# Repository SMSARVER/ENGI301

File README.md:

<h1>ENGI301</h1>
<p>Repository for ENGI301 course work</p>

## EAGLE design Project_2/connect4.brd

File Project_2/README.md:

Please read me or else:

This directory contains the files (library, board, schematic, manufacturing) for a custom PCB for my Robot V.S. Human Connect 4 Robot. Please learn more about my project here: https://www.hackster.io/samuelmsarver/robot-v-s-human-connect-4-eca0b5

This PCB was made using EAGLE and contains all components for the robot except for the stepper motor and servo motor (which are attatched externally).

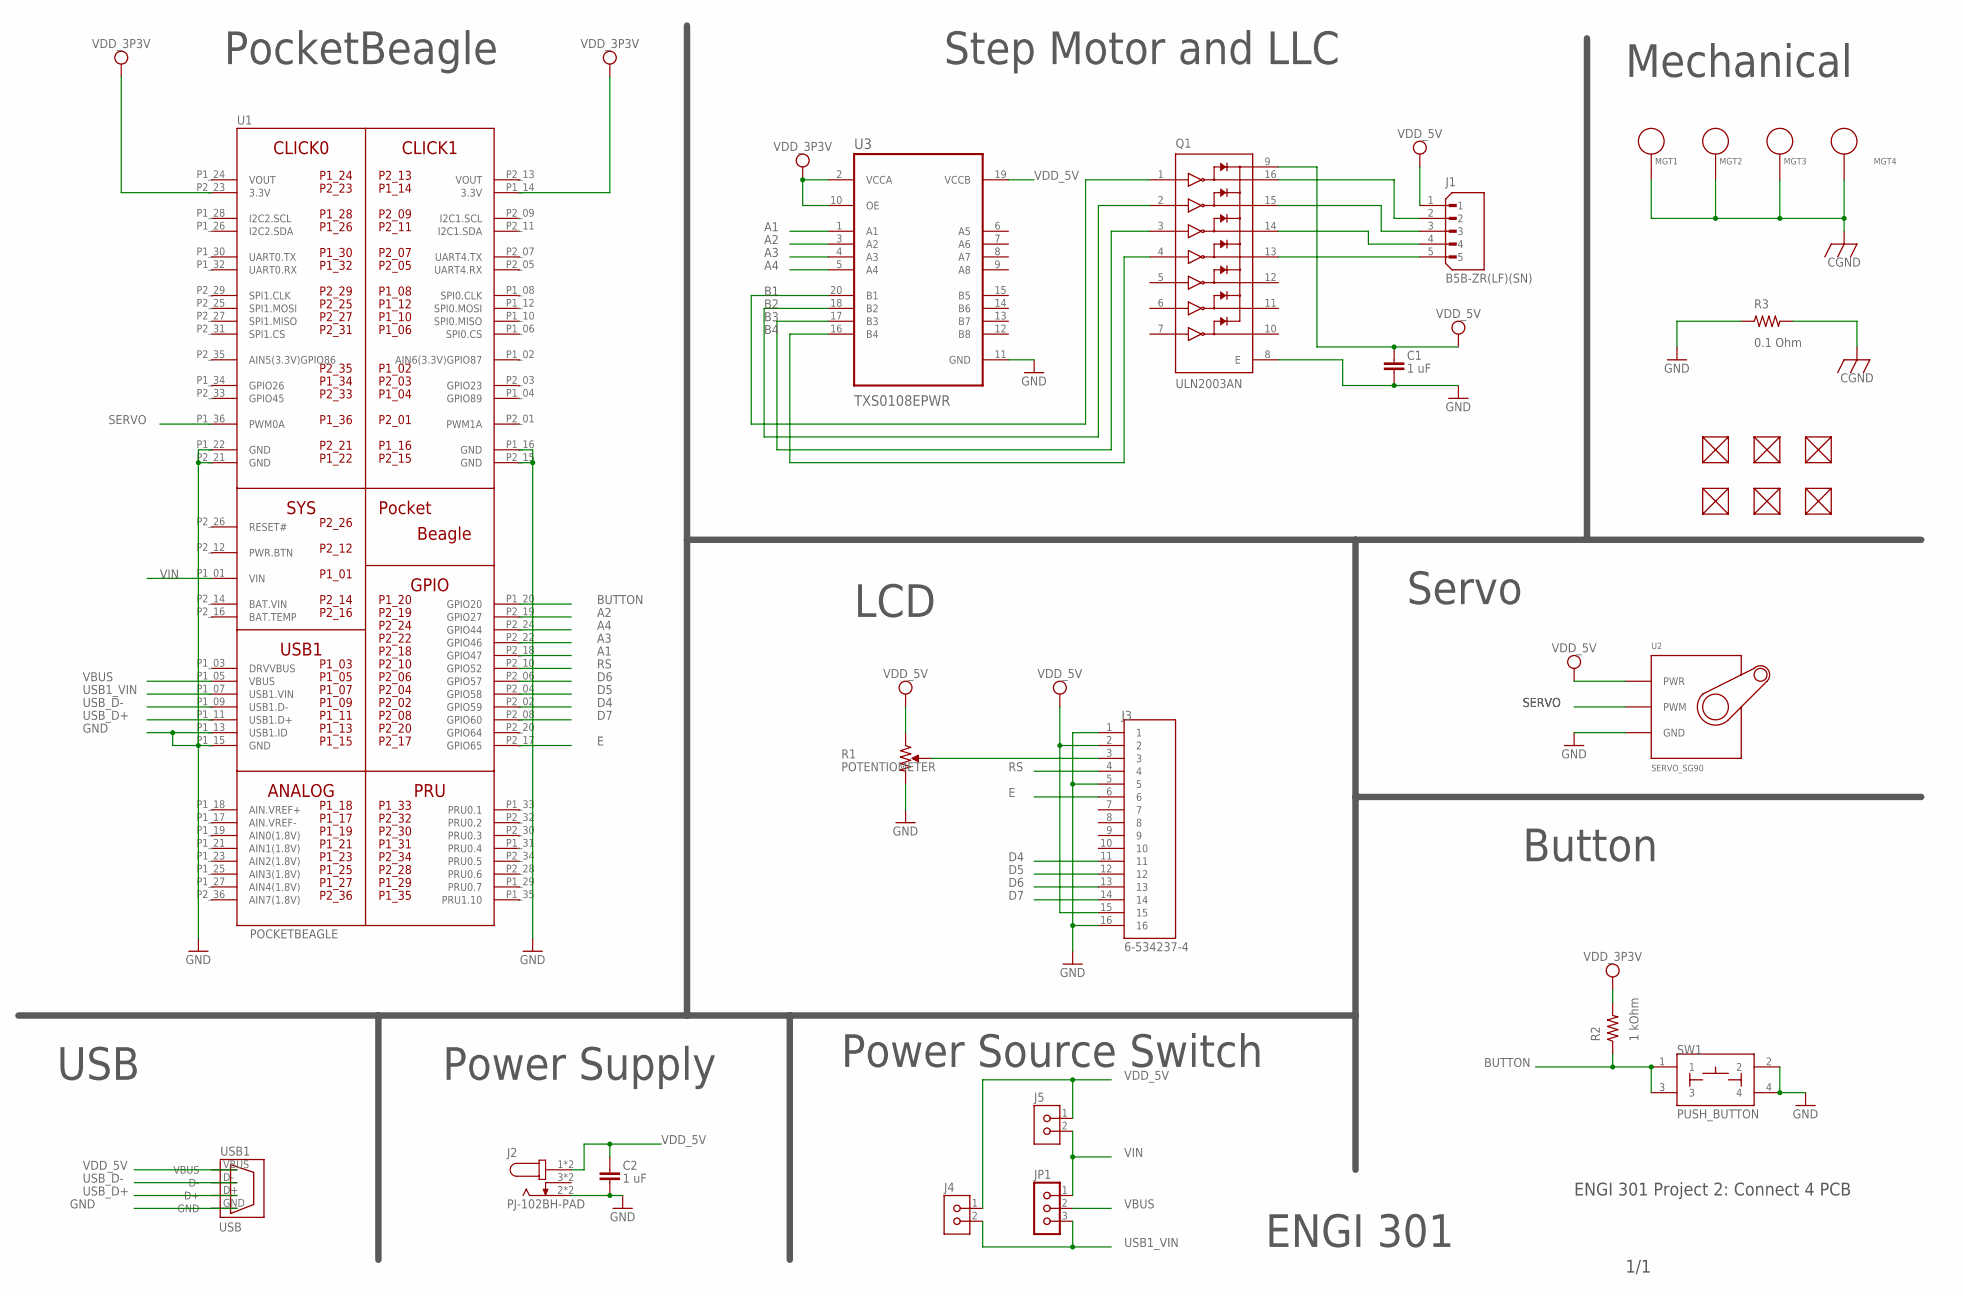
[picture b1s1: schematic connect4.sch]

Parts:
C1, C2: 1 uF; C0402
FUD1, FUD2, FUD3, FUD4, FUD5, FUD6: FIDUCIAL; FIDUCIAL_40MIL
J1: B5B-ZR(LF)(SN); JST_B5B-ZR(LF)(SN)
J2: PJ-102BH-PAD; CUI_PJ-102BH-DIM-SMT-PAD
J3: 6-534237-4; TE_6-534237-4
J4, J5: PINHD-1X2; H1X2-2.54
JP1: PINHD-1X3; H1X3-2.54
MGT1, MGT2, MGT3, MGT4: MOUNTING_HOLE
Q1: ULN2003AN; DIP794W45P254L1969H508Q16
R1: POTENTIOMETER; POT-PO90S
R2: 1 kOhm; R0603
R3: 0.1 Ohm; R0805
SW1: PUSH_BUTTON; BUTTON_12.5MM
U1: POCKETBEAGLE
U2: SERVO_SG90; SERVO-X1
U3: TXS0108EPWR; SOP65P640X120-20N
USB1: USB

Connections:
A1: U1.P2_18 (GPIO47), U3.1 (A1)
A2: U1.P2_19 (GPIO27), U3.3 (A2)
A3: U1.P2_22 (GPIO46), U3.4 (A3)
A4: U1.P2_24 (GPIO44), U3.5 (A4)
B1: Q1.1 (1B), U3.20 (B1)
B2: Q1.2 (2B), U3.18 (B2)
B3: Q1.3 (3B), U3.17 (B3)
B4: Q1.4 (4B), U3.16 (B4)
BAT.VIN: U1.P2_14 (BAT.VIN)
BUTTON: R2.1, SW1.1, SW1.3, U1.P1_20 (GPIO20)
CGND: MGT1.P$1, MGT2.P$1, MGT3.P$1, MGT4.P$1, R3.2
D4: J3.11, U1.P2_02 (GPIO59)
D5: J3.12, U1.P2_04 (GPIO58)
D6: J3.13, U1.P2_06 (GPIO57)
D7: J3.14, U1.P2_08 (GPIO60)
E: J3.6, U1.P2_17 (GPIO65)
GND: C1.2, C2.2, J2.2, J2.2_B (2), J3.1, J3.5, J3.16, Q1.8 (E), R1.CW, R3.1, SW1.2, SW1.4, U1.P1_13 (USB1.ID), U1.P1_15 (GND), U1.P1_16 (GND), U1.P1_22 (GND), U1.P2_15 (GND), U1.P2_21 (GND), U2.GND, U3.11 (GND), USB1.GND
unnamed: J1.2, Q1.16 (1C)
unnamed: J1.3, Q1.15 (2C)
unnamed: J3.3, R1.S
unnamed: J1.4, Q1.14 (3C)
unnamed: J1.5, Q1.13 (4C)
RS: J3.4, U1.P2_10 (GPIO52)
SERVO: U1.P1_36 (PWM0A), U2.SIG (PWM)
USB1_VIN: J4.2, JP1.3, U1.P1_07 (USB1.VIN)
USB_D+: U1.P1_11 (USB1.D+), USB1.D+
USB_D-: U1.P1_09 (USB1.D-), USB1.D-
VBUS: JP1.2, U1.P1_05 (VBUS)
VDD_3P3V: R2.2, U1.P1_14 (3.3V), U1.P2_23 (3.3V), U3.2 (VCCA), U3.10 (OE)
VDD_5V: C1.1, C2.1, J1.1, J2.1, J2.1_B (1), J3.2, J3.15, J4.1, J5.1, Q1.9 (COM), R1.CCW, U2.PWR, U3.19 (VCCB), USB1.VBUS
VIN: J5.2, JP1.1, U1.P1_01 (VIN)
VOUT: U1.P1_24 (VOUT), U1.P2_13 (VOUT)

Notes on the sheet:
PocketBeagle
Step Motor and LLC
LCD
USB
Power Supply
Power Source Switch
Button
Servo
Mechanical
ENGI 301
ENGI 301 Project 2: Connect 4 PCB
1/1

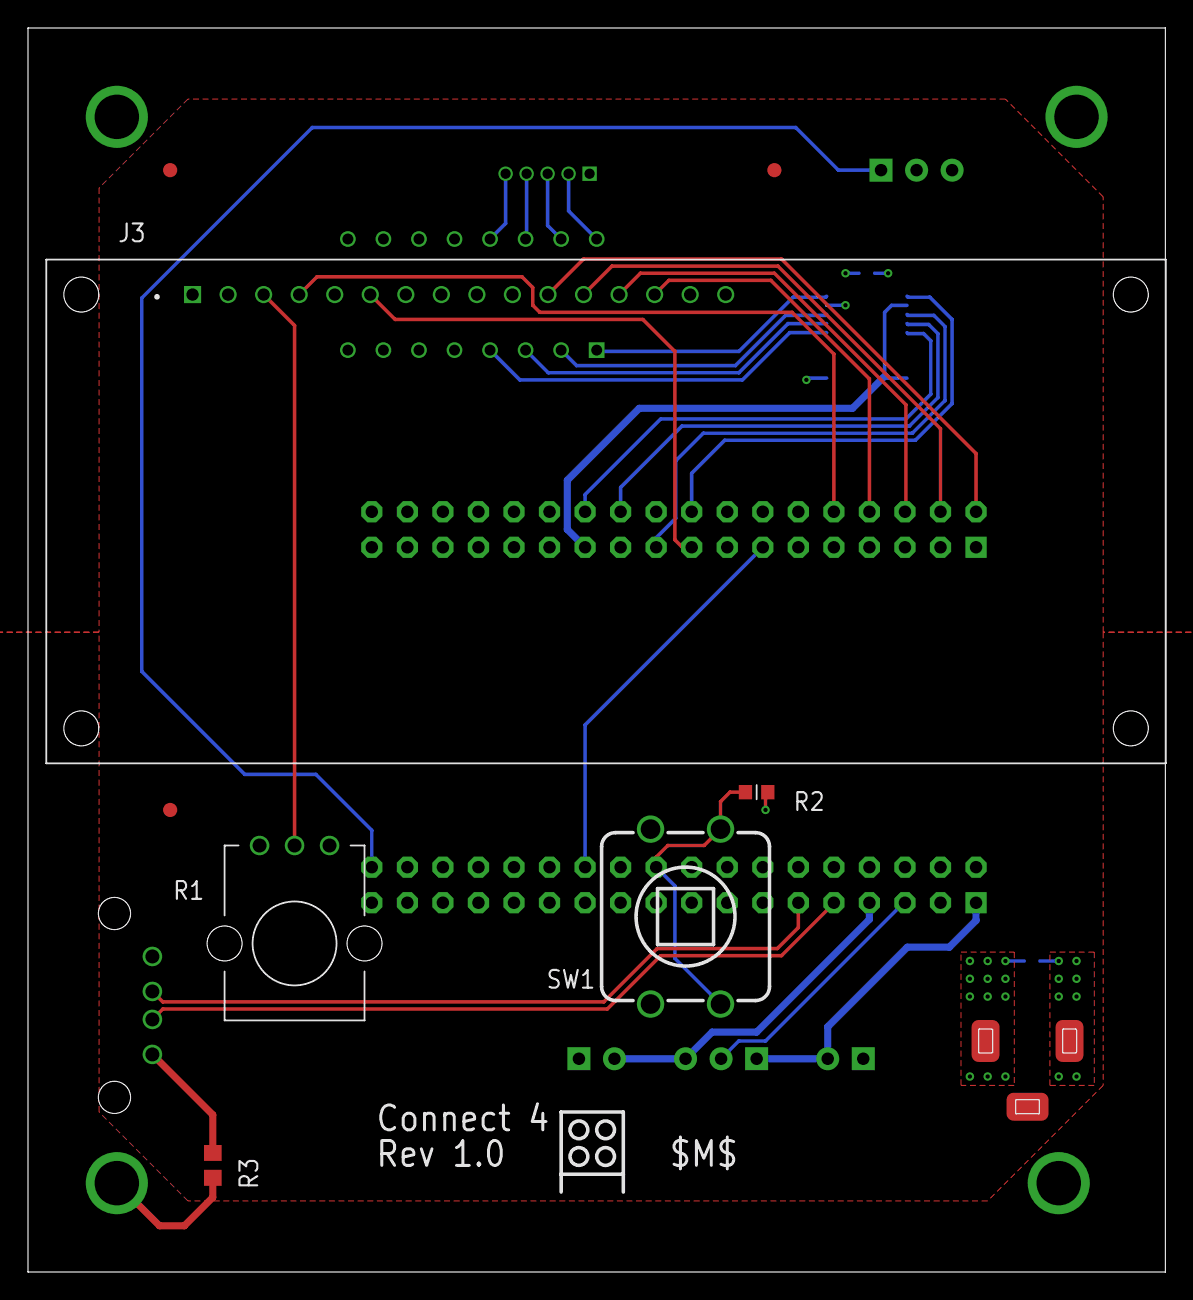
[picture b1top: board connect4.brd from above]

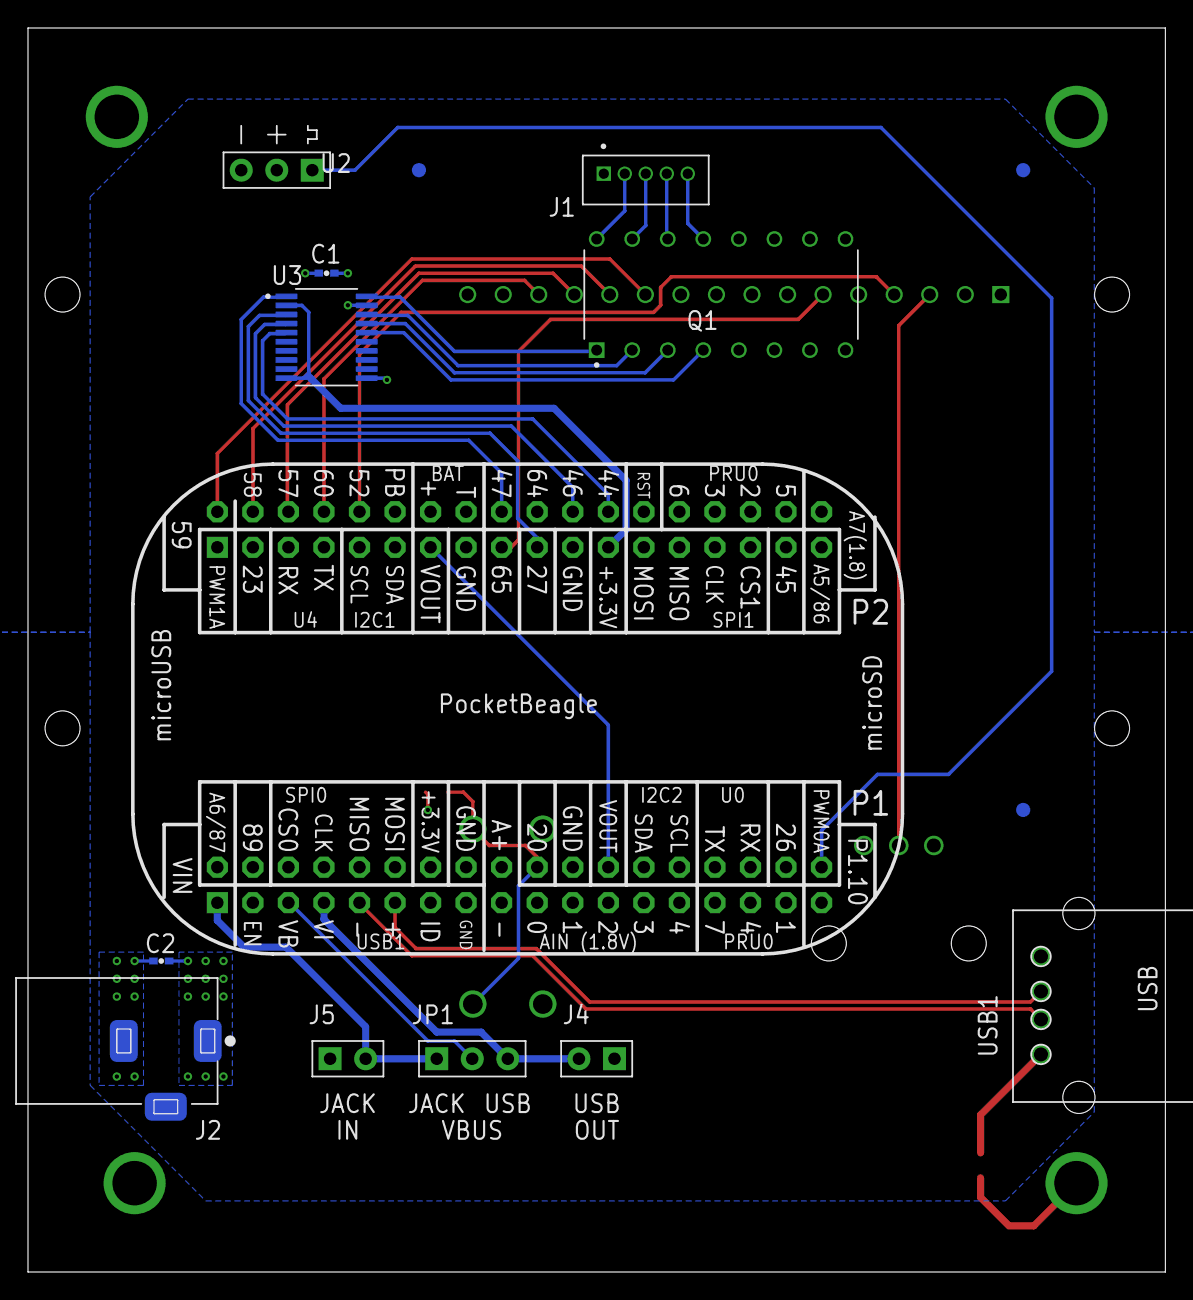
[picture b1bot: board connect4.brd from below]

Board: 4 copper layers, 81.3 x 88.9 mm, 27 parts (15 on the bottom side), 31 nets.

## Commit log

2022-01-26 Updating README.md
    Updating README.md
2022-02-12 created python simple calc directory with file from class
2022-02-13 assignment 4
    added additional features to simple calc
2022-02-13 created blink usr3
    assignment 4
2022-02-21 moving files into directory
2022-02-21 testing pushing
2022-03-21 connected sensors, wrote opencv code
2022-04-05 final connect 4 code
    final connect 4 code w/opencv
2022-04-05 created README
2022-05-02 added all files
2022-08-16 project update
